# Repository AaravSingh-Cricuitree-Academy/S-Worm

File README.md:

# S-Worm
_Swarm based Watch operations for rescue missions_

## Basic architechtural overview-
Essentially its a system of 2 different types of drones
1) The recon
2) The rescuer
   
And also

-> Ground station

-> The ground station uses TDMA architechture to direct ALL the drones.

-> This is intended to be used in situations of disaster like earthquakes, tsunamis, bombings ,and/or mapping out complex terrain. 

Both share the same flight controller and ESC board. The difference in them is speciality boards which are unique to the respective drone, defined below-

-> The recon's speciality board is equiped with a Camera and LIDAR which hovers over terrain to map it out and then stores it. After a full map out it sends the data to the ground station where the data is processed and the area is divided into zones and high risk areas.

-> The rescue is equipped with a Mic, GPR to, Thermal and regular camera all processed by a PI hat 2 to look for human signals even under debris.

_Check [Hardware ReadMe](Hardware/Hardware_ReadMe.md) to have an in-depth
 overview of exactly what has been built ;)_

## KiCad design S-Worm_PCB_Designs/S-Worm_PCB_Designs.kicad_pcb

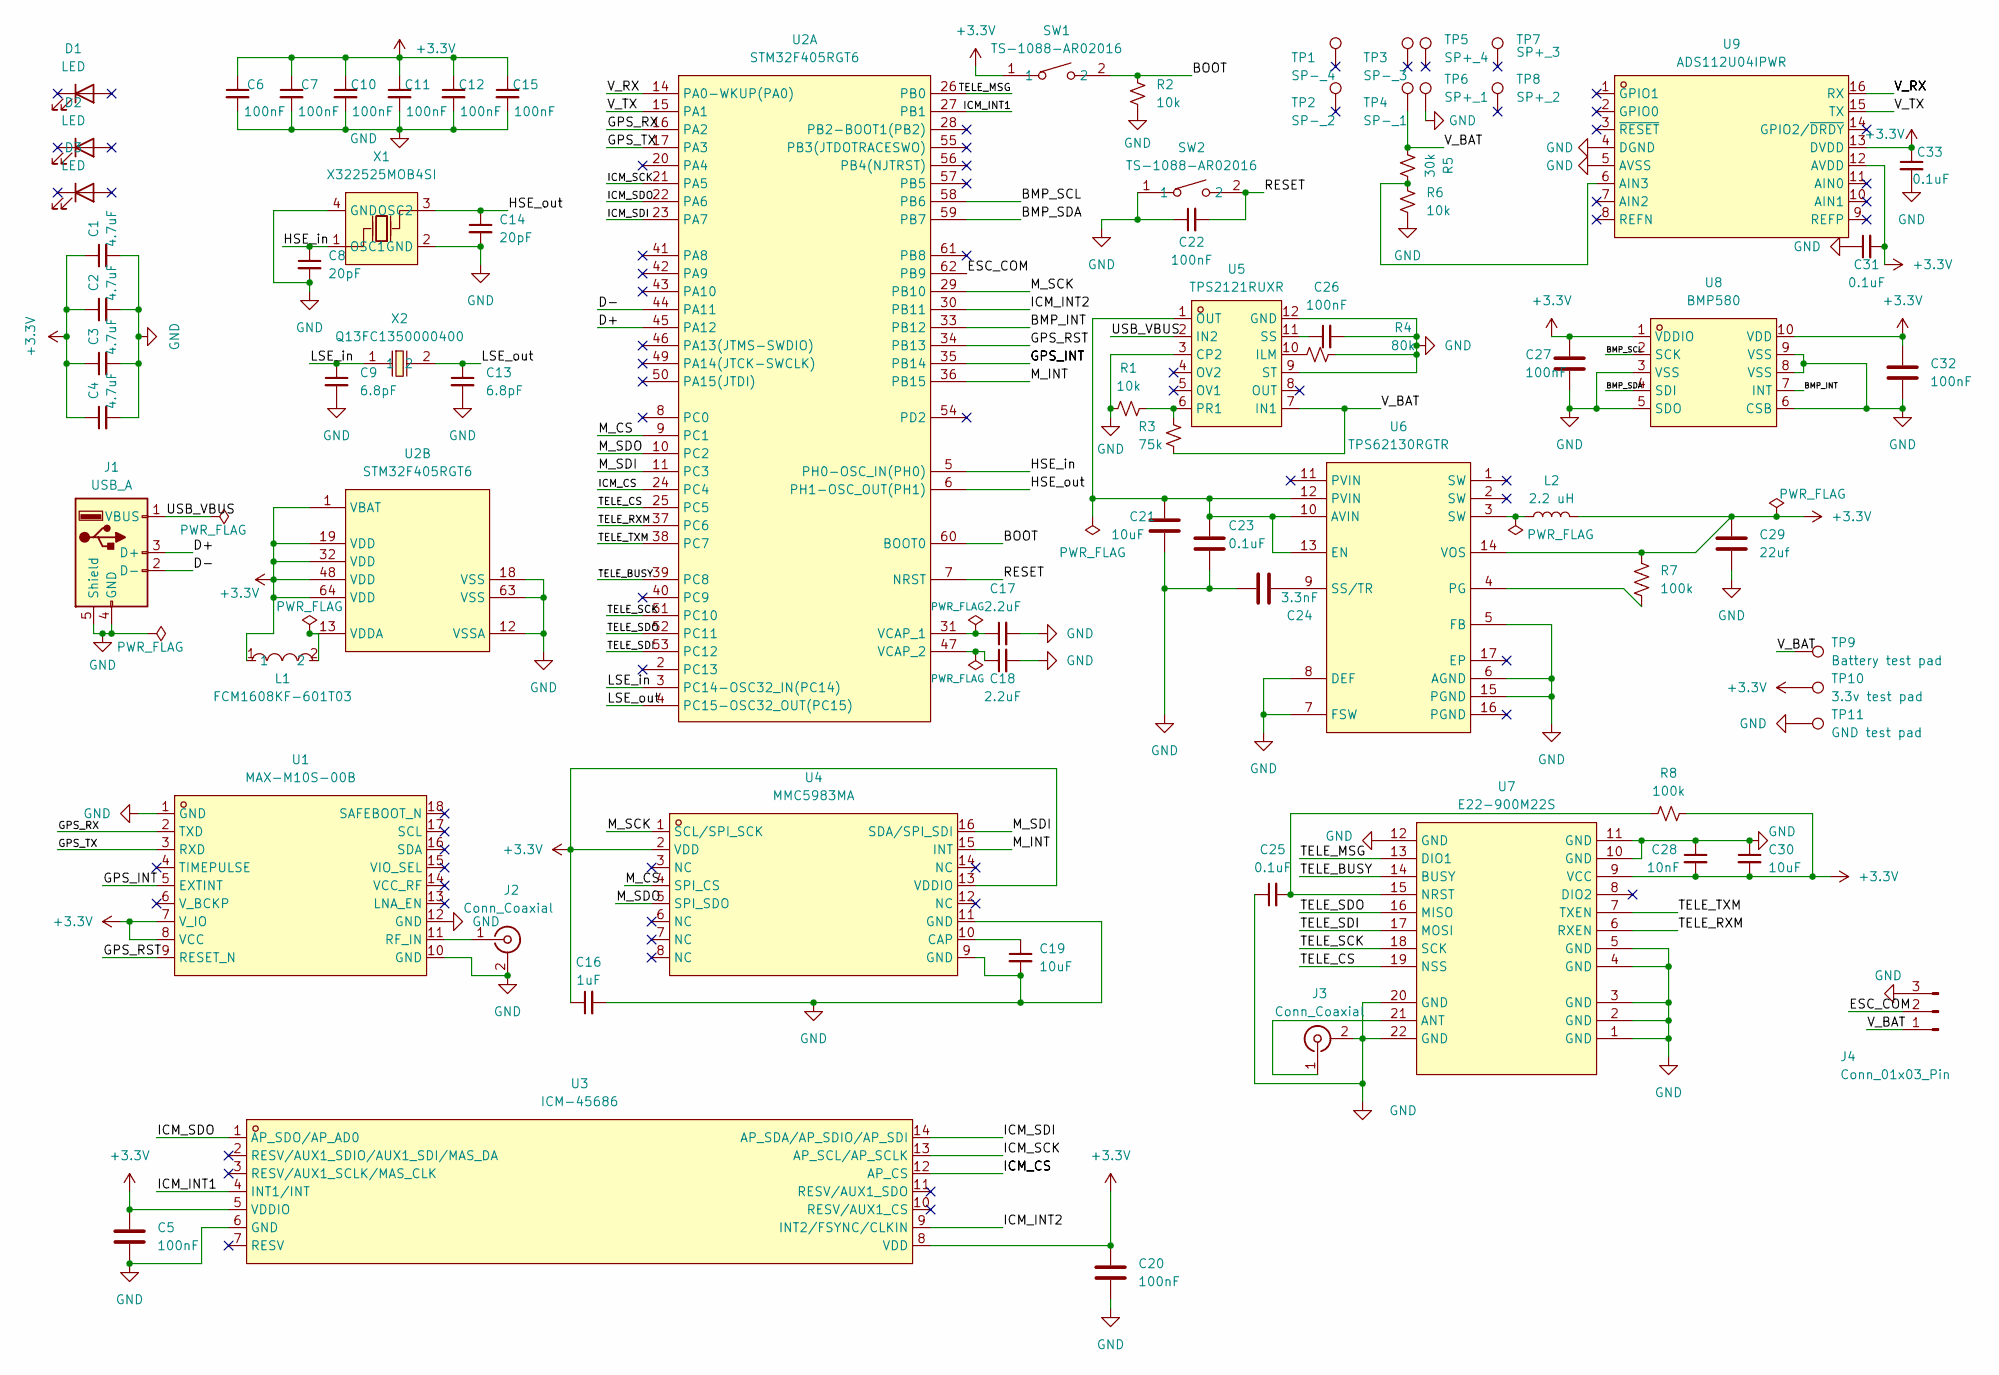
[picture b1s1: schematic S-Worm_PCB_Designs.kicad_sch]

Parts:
C1, C2, C3, C4: 4.7uF; C_0402_1005Metric
C5, C6, C7, C10, C11, C12, C15, C20, C22, C26, C27, C32: 100nF; C_0402_1005Metric
C8, C14: 20pF; C_0402_1005Metric
C9, C13: 6.8pF; C_0402_1005Metric
C16: 1uF; C_0402_1005Metric
C17, C18: 2.2uF; C_0402_1005Metric
C19: 10uF; C_0805_2012Metric
C21, C30: 10uF; C_0402_1005Metric
C23, C25, C31, C33: 0.1uF; C_0402_1005Metric
C24: 3.3nF; C_0402_1005Metric
C28: 10nF; C_0402_1005Metric
C29: 22uf; C_0402_1005Metric
D1, D2, D3: LED; LED_0805_2012Metric
J1: USB_A; USB_A_CNCTech_1001-011-01101_Horizontal
J2, J3: Conn_Coaxial; U.FL_Hirose_U.FL-R-SMT-1_Vertical
J4: Conn_01x03_Pin; JST_ACH_BM03B-ACHSS-GAN-ETF_1x03-1MP_P1.20mm_Vertical
L1: FCM1608KF-601T03; L0603; MPN FCM1608KF-601T03; LCSC Part C141723
L2: 2.2 uH; L_0201_0603Metric
R1, R2: 10k; R_0201_0603Metric
R3: 75k; R_0402_1005Metric
R4: 80k; R_0402_1005Metric
R5: 30k; R_0402_1005Metric
R6: 10k; R_0402_1005Metric
R7, R8: 100k; R_0402_1005Metric
SW1, SW2: TS-1088-AR02016; SW-SMD_L3.9-W3.0-P4.45; MPN TS-1088-AR02016; LCSC Part C720477
TP1: SP-_4; TestPoint_Pad_4.0x4.0mm
TP2: SP-_2; TestPoint_Pad_4.0x4.0mm
TP3: SP-_3; TestPoint_Pad_4.0x4.0mm
TP4: SP-_1; TestPoint_Pad_4.0x4.0mm
TP5: SP+_4; TestPoint_Pad_4.0x4.0mm
TP6: SP+_1; TestPoint_Pad_4.0x4.0mm
TP7: SP+_3; TestPoint_Pad_4.0x4.0mm
TP8: SP+_2; TestPoint_Pad_4.0x4.0mm
TP9: Battery test pad; TestPoint_Pad_4.0x4.0mm
TP10: 3.3v test pad; TestPoint_Pad_4.0x4.0mm
TP11: GND test pad; TestPoint_Pad_4.0x4.0mm
U1: MAX-M10S-00B; SMD-18_L10.1-W9.7-P1.10-TL_SKG09F; MPN MAX-M10S-00B; LCSC Part C4153167
U2: STM32F405RGT6; LQFP-64_L10.0-W10.0-P0.50-LS12.0-BL; MPN STM32F405RGT6; LCSC Part C15742
U3: ICM-45686; LGA-14_L3.0-W2.5-P0.50-TL; MPN ICM-45686; LCSC Part C22459454
U4: MMC5983MA; LGA-16_L3.0-W3.0-P0.50-BL_SQ; MPN MMC5983MA; LCSC Part C404329
U5: TPS2121RUXR; VQFN-HR-12_L2.5-W2.0-P0.50-BL; MPN TPS2121RUXR; LCSC Part C485916
U6: TPS62130RGTR; QFN-16_L3.0-W3.0-P0.50-TL-EP1.7; MPN TPS62130RGTR; LCSC Part C43590
U7: E22-900M22S; WIRELM-SMD_E22-900M22S; MPN E22-900M22S; LCSC Part C411293
U8: BMP580; LGA-10_L2.0-W2.0-P0.50-TL_BMP580; MPN BMP580; LCSC Part C22391138
U9: ADS112U04IPWR; TSSOP-16_L5.0-W4.4-P0.65-LS6.4-BL; MPN ADS112U04IPWR; LCSC Part C701616
X1: X322525MOB4SI; CRYSTAL-SMD_4P-L3.2-W2.5-BL; MPN X322525MOB4SI; LCSC Part C9006
X2: Q13FC1350000400; FC-135R_L3.2-W1.5; MPN Q13FC13500004; LCSC Part C32346

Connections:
+3.3V: C1.1, C2.1, C3.1, C4.1, C5.1, C6.1, C7.1, C10.1, C11.1, C12.1, C15.1, C16.1, C20.1, C27.1, C28.2, C29.1, C30.2, C31.2, C32.1, C33.1, L1.1, L2.2, R7.1, R8.2, SW1.1, TP10.1, U1.7 (V_IO), U1.8 (VCC), U2.1 (VBAT), U2.19 (VDD), U2.32 (VDD), U2.48 (VDD), U2.64 (VDD), U3.5 (VDDIO), U3.8 (VDD), U4.2 (VDD), U4.13 (VDDIO), U6.14 (VOS), U7.9 (VCC), U8.1 (VDDIO), U8.10 (VDD), U9.12 (AVDD), U9.13 (DVDD)
/BMP_INT: U2.33 (PB12), U8.7 (INT)
/BMP_SCL: U2.58 (PB6), U8.2 (SCK)
/BMP_SDA: U2.59 (PB7), U8.4 (SDI)
/BOOT: R2.1, SW1.2, U2.60 (BOOT0)
/D+: J1.3 (D+), U2.45 (PA12)
/D-: J1.2 (D-), U2.44 (PA11)
/ESC_COM: J4.2, U2.62 (PB9)
/GPS_INT: U1.5 (EXTINT), U2.35 (PB14)
/GPS_RST: U1.9 (RESET_N), U2.34 (PB13)
/GPS_RX: U1.2 (TXD), U2.16 (PA2)
/GPS_TX: U1.3 (RXD), U2.17 (PA3)
/HSE_in: C8.1, U2.5 (PH0-OSC_IN(PH0)), X1.1 (OSC1)
/HSE_out: C14.1, U2.6 (PH1-OSC_OUT(PH1)), X1.3 (OSC2)
/ICM_CS: U2.24 (PC4), U3.12 (AP_CS)
/ICM_INT1: U2.27 (PB1), U3.4 (INT1/INT)
/ICM_INT2: U2.30 (PB11), U3.9 (INT2/FSYNC/CLKIN)
/ICM_SCK: U2.21 (PA5), U3.13 (AP_SCL/AP_SCLK)
/ICM_SDI: U2.23 (PA7), U3.14 (AP_SDA/AP_SDIO/AP_SDI)
/ICM_SDO: U2.22 (PA6), U3.1 (AP_SDO/AP_AD0)
/LSE_in: C9.1, U2.3 (PC14-OSC32_IN(PC14)), X2.1
/LSE_out: C13.1, U2.4 (PC15-OSC32_OUT(PC15)), X2.2
/M_CS: U2.9 (PC1), U4.4 (SPI_CS)
/M_INT: U2.36 (PB15), U4.15 (INT)
/M_SCK: U2.29 (PB10), U4.1 (SCL/SPI_SCK)
/M_SDI: U2.11 (PC3), U4.16 (SDA/SPI_SDI)
/M_SDO: U2.10 (PC2), U4.5 (SPI_SDO)
/RESET: C22.2, SW2.2, U2.7 (NRST)
/TELE_BUSY: U2.39 (PC8), U7.14 (BUSY)
/TELE_CS: U2.25 (PC5), U7.19 (NSS)
/TELE_MSG: U2.26 (PB0), U7.13 (DIO1)
/TELE_RXM: U2.37 (PC6), U7.6 (RXEN)
/TELE_SCK: U2.51 (PC10), U7.18 (SCK)
/TELE_SDI: U2.53 (PC12), U7.17 (MOSI)
/TELE_SDO: U2.52 (PC11), U7.16 (MISO)
/TELE_TXM: U2.38 (PC7), U7.7 (TXEN)
/USB_VBUS: J1.1 (VBUS), U5.2 (IN2)
/V_BAT: J4.1, R3.2, R5.1, TP4.1, TP9.1, U5.7 (IN1)
/V_RX: U2.14 (PA0-WKUP(PA0)), U9.16 (RX)
/V_TX: U2.15 (PA1), U9.15 (TX)
GND: C1.2, C2.2, C3.2, C4.2, C5.2, C6.2, C7.2, C8.2, C9.2, C10.2, C11.2, C12.2, C13.2, C14.2, C15.2, C16.2, C17.2, C18.2, C19.2, C20.2, C21.2, C22.1, C23.2, C24.2, C25.1, C26.2, C27.2, C28.1, C29.2, C30.1, C31.1, C32.2, C33.2, J1.4 (GND), J1.5 (Shield), J2.2 (Ext), J3.2 (Ext), J4.3, J4.MP, R1.1, R2.2, R4.2, R6.2, SW2.1, TP6.1, TP11.1, U1.1 (GND), U1.10 (GND), U1.12 (GND), U2.12 (VSSA), U2.18 (VSS), U2.63 (VSS), U3.6 (GND), U4.9 (GND), U4.11 (GND), U5.3 (CP2), U5.9 (ST), U5.12 (GND), U6.5 (FB), U6.6 (AGND), U6.7 (FSW), U6.8 (DEF), U6.15 (PGND), U7.1 (GND), U7.2 (GND), U7.3 (GND), U7.4 (GND), U7.5 (GND), U7.10 (GND), U7.11 (GND), U7.12 (GND), U7.20 (GND), U7.22 (GND), U8.3 (VSS), U8.5 (SDO), U8.6 (CSB), U8.8 (VSS), U8.9 (VSS), U9.4 (DGND), U9.5 (AVSS), X1.2 (GND), X1.4 (GND)
unnamed: J2.1 (In), U1.11 (RF_IN)
unnamed: J3.1 (In), U7.21 (ANT)
unnamed: L2.1, U6.3 (SW)
unnamed: C17.1, U2.31 (VCAP_1)
unnamed: C18.1, U2.47 (VCAP_2)
unnamed: L1.2, U2.13 (VDDA)
unnamed: C19.1, U4.10 (CAP)
unnamed: R4.1, U5.10 (ILM)
unnamed: R1.2, R3.1, U5.6 (PR1)
unnamed: C26.1, U5.11 (SS)
unnamed: C21.1, C23.1, U5.1 (OUT), U6.10 (AVIN), U6.12 (PVIN), U6.13 (EN)
unnamed: R7.2, U6.4 (PG)
unnamed: C24.1, U6.9 (SS/TR)
unnamed: C25.2, R8.1, U7.15 (NRST)
unnamed: R5.2, R6.1, U9.6 (AIN3)

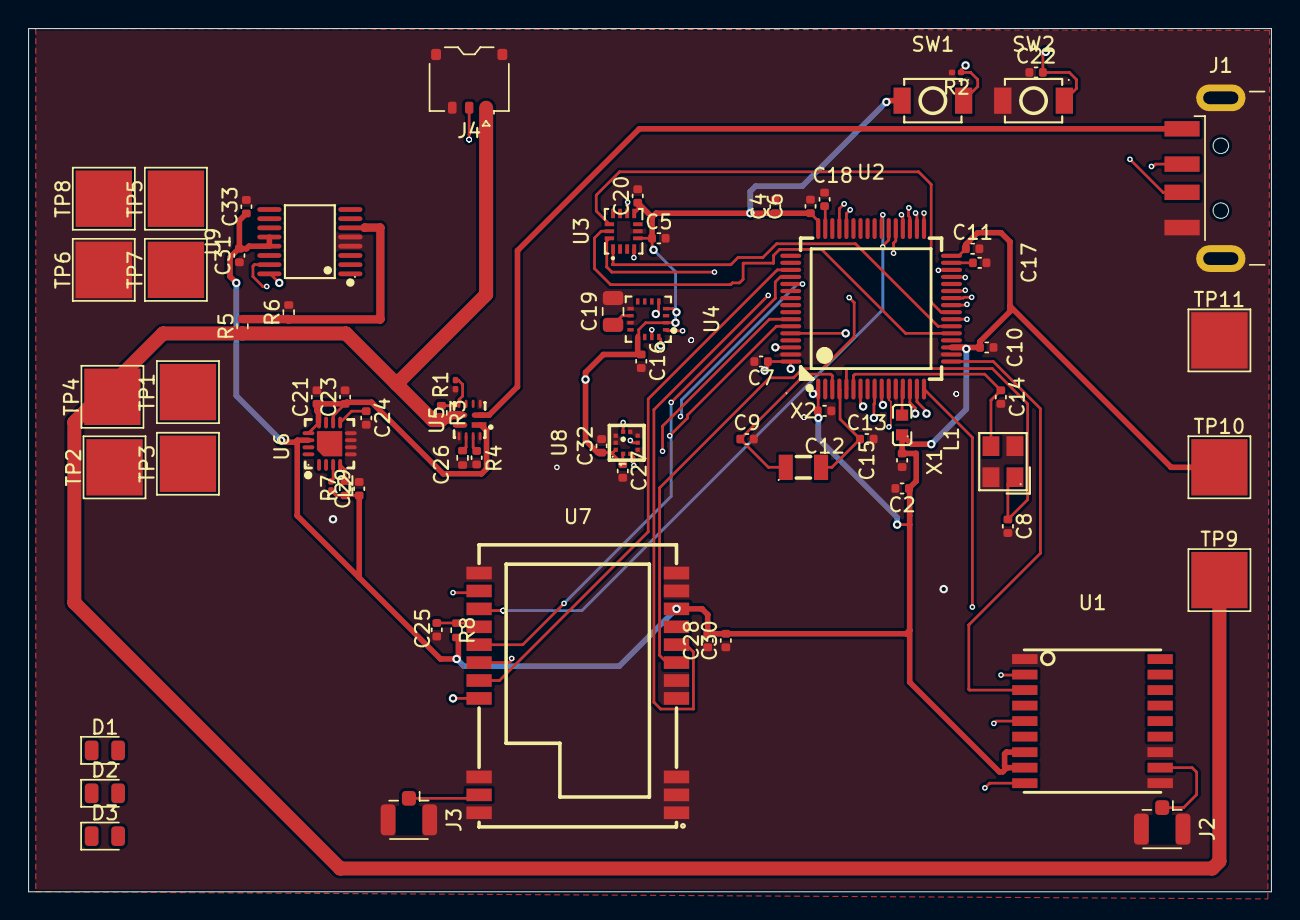
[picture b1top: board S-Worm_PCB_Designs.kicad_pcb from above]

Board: 4 copper layers, 88.1 x 61.2 mm, 72 parts (0 on the bottom side), 56 nets.

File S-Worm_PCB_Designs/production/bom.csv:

Designator,Footprint,Quantity,Value,LCSC Part #
"C10, C11, C12, C15, C20, C22, C26, C27, C32, C5, C6, C7",0402,12,100nF,
"C13, C9",0402,2,6.8pF,
"C14, C8",0402,2,20pF,
C16,0402,1,1uF,
"C17, C18",0402,2,2.2uF,
C19,0805,1,10uF,
"C2, C4",0402,2,4.7uF,
"C21, C30",0402,2,10uF,
"C23, C25, C31, C33",0402,4,0.1uF,
C24,0402,1,3.3nF,
C28,0402,1,10nF,
C29,0402,1,22uf,
"D1, D2, D3",0805,3,LED,
J1,USB_A_CNCTech_1001-011-01101_Horizontal,1,USB_A,
"J2, J3",U.FL_Hirose_U.FL-R-SMT-1_Vertical,2,Conn_Coaxial,
J4,JST_ACH_BM03B-ACHSS-GAN-ETF_1x03-1MP_P1.20mm_Vertical,1,Conn_01x03_Pin,
L1,L0603,1,FCM1608KF-601T03,C141723
L2,0201,1,2.2 uH,
"R1, R2",0201,2,10k,
R3,0402,1,75k,
R4,0402,1,80k,
R5,0402,1,30k,
R6,0402,1,10k,
"R7, R8",0402,2,100k,
"SW1, SW2",SW-SMD_L3.9-W3.0-P4.45,2,TS-1088-AR02016,C720477
TP1,TestPoint_Pad_4.0x4.0mm,1,SP-_4,
TP10,TestPoint_Pad_4.0x4.0mm,1,3.3v test pad,
TP11,TestPoint_Pad_4.0x4.0mm,1,GND test pad,
TP2,TestPoint_Pad_4.0x4.0mm,1,SP-_2,
TP3,TestPoint_Pad_4.0x4.0mm,1,SP-_3,
TP4,TestPoint_Pad_4.0x4.0mm,1,SP-_1,
TP5,TestPoint_Pad_4.0x4.0mm,1,SP+_4,
TP6,TestPoint_Pad_4.0x4.0mm,1,SP+_1,
TP7,TestPoint_Pad_4.0x4.0mm,1,SP+_3,
TP8,TestPoint_Pad_4.0x4.0mm,1,SP+_2,
TP9,TestPoint_Pad_4.0x4.0mm,1,Battery test pad,
U1,SMD-18_L10.1-W9.7-P1.10-TL_SKG09F,1,MAX-M10S-00B,C4153167
U2,LQFP-64_L10.0-W10.0-P0.50-LS12.0-BL,1,STM32F405RGT6,C15742
U3,LGA-14_L3.0-W2.5-P0.50-TL,1,ICM-45686,C22459454
U4,LGA-16_L3.0-W3.0-P0.50-BL_SQ,1,MMC5983MA,C404329
U5,VQFN-HR-12_L2.5-W2.0-P0.50-BL,1,TPS2121RUXR,C485916
U6,QFN-16_L3.0-W3.0-P0.50-TL-EP1.7,1,TPS62130RGTR,C43590
U7,WIRELM-SMD_E22-900M22S,1,E22-900M22S,C411293
U8,LGA-10_L2.0-W2.0-P0.50-TL_BMP580,1,BMP580,C22391138
U9,TSSOP-16_L5.0-W4.4-P0.65-LS6.4-BL,1,ADS112U04IPWR,C701616
X1,CRYSTAL-SMD_4P-L3.2-W2.5-BL,1,X322525MOB4SI,C9006
X2,FC-135R_L3.2-W1.5,1,Q13FC1350000400,C32346

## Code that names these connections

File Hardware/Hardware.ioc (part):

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Mcu.Name=STM32F405RGTx
Mcu.Package=LQFP64
Mcu.UserName=STM32F405RGTx
PA0-WKUP.GPIOParameters=GPIO_Label
PA0-WKUP.GPIO_Label=V_TX
PA0-WKUP.Mode=Asynchronous
PA0-WKUP.Signal=UART4_TX
PA1.GPIOParameters=GPIO_Label
PA1.GPIO_Label=V_RX
PA1.Mode=Asynchronous
PA1.Signal=UART4_RX
PA11.Mode=Device_Only
PA11.Signal=USB_OTG_FS_DM
PA12.Mode=Device_Only
PA12.Signal=USB_OTG_FS_DP
PA2.GPIOParameters=GPIO_Label
PA2.GPIO_Label=GPS_TX
PA2.Mode=Asynchronous
PA2.Signal=USART2_TX
PA3.GPIOParameters=GPIO_Label
PA3.GPIO_Label=GPS_RX
PA3.Mode=Asynchronous
PA3.Signal=USART2_RX
PA5.GPIOParameters=GPIO_Label
PA5.GPIO_Label=IMU_SCK
PA5.Mode=Full_Duplex_Master
PA5.Signal=SPI1_SCK
PA6.GPIOParameters=GPIO_Label
PA6.GPIO_Label=IMU_SDO
PA6.Mode=Full_Duplex_Master
PA6.Signal=SPI1_MISO
PA7.GPIOParameters=GPIO_Label
PA7.GPIO_Label=IMU_SDI
PA7.Mode=Full_Duplex_Master
PA7.Signal=SPI1_MOSI
PA9.GPIOParameters=GPIO_Label
PA9.GPIO_Label=ESC_COM
PA9.Mode=Half_duplex(single_wire_mode)
PA9.Signal=USART1_TX
PB0.GPIOParameters=GPIO_Label
PB0.GPIO_Label=TELE_MSG
PB0.Signal=GPIO_Output
PB1.GPIOParameters=GPIO_Label
PB1.GPIO_Label=IMU_INT1
PB1.Signal=GPXTI1
PB10.GPIOParameters=GPIO_Label
PB10.GPIO_Label=M_SCK
PB10.Mode=Full_Duplex_Master
PB10.Signal=SPI2_SCK
PB11.GPIOParameters=GPIO_Label
PB11.GPIO_Label=IMU_INT2
PB11.Signal=GPXTI11
PB12.GPIOParameters=GPIO_Label
PB12.GPIO_Label=BMP_INT
PB12.Signal=GPXTI12
PB13.GPIOParameters=GPIO_Label
PB13.GPIO_Label=GPS_RST
PB13.Signal=GPIO_Output
PB14.GPIOParameters=GPIO_Label
PB14.GPIO_Label=GPS_INT
PB14.Signal=GPXTI14
PB15.GPIOParameters=GPIO_Label
PB15.GPIO_Label=M_INT
PB15.Signal=GPXTI15
PB5.Mode=SMBus-Alert-mode
PB5.Signal=I2C1_SMBA
PB6.GPIOParameters=GPIO_Label
PB6.GPIO_Label=BMP_SCL
PB6.Mode=SMBus-Alert-mode
PB6.Signal=I2C1_SCL
PB7.GPIOParameters=GPIO_Label
PB7.GPIO_Label=BMP_SDA
PB7.Mode=SMBus-Alert-mode
PB7.Signal=I2C1_SDA
PC1.GPIOParameters=GPIO_Label
PC1.GPIO_Label=M_CS
PC1.Signal=GPIO_Output
PC10.GPIOParameters=GPIO_Label
PC10.GPIO_Label=TELE_SCK
PC10.Mode=Full_Duplex_Master
PC10.Signal=SPI3_SCK
PC11.GPIOParameters=GPIO_Label
PC11.GPIO_Label=TELE_SDO
PC11.Mode=Full_Duplex_Master
PC11.Signal=SPI3_MISO
PC12.GPIOParameters=GPIO_Label
PC12.GPIO_Label=TELE_SDI
PC12.Mode=Full_Duplex_Master
PC12.Signal=SPI3_MOSI
PC14-OSC32_IN.GPIOParameters=GPIO_Label
PC14-OSC32_IN.GPIO_Label=LSE_IN
PC14-OSC32_IN.Mode=LSE-External-Oscillator
PC14-OSC32_IN.Signal=RCC_OSC32_IN
PC15-OSC32_OUT.GPIOParameters=GPIO_Label
PC15-OSC32_OUT.GPIO_Label=LSE_OUT
PC15-OSC32_OUT.Mode=LSE-External-Oscillator
PC15-OSC32_OUT.Signal=RCC_OSC32_OUT
PC2.GPIOParameters=GPIO_Label
PC2.GPIO_Label=M_SDO
PC2.Mode=Full_Duplex_Master
PC2.Signal=SPI2_MISO
PC3.GPIOParameters=GPIO_Label
PC3.GPIO_Label=M_SDI
PC3.Mode=Full_Duplex_Master
PC3.Signal=SPI2_MOSI
PC4.GPIOParameters=GPIO_Label
PC4.GPIO_Label=IMU_CS
PC4.Signal=GPIO_Output
PC5.GPIOParameters=GPIO_Label
PC5.GPIO_Label=TELE_CS
PC5.Signal=GPIO_Output
PC6.GPIOParameters=GPIO_Label
PC6.GPIO_Label=TELE_RXM
PC6.Signal=GPIO_Output
PC7.GPIOParameters=GPIO_Label
PC7.GPIO_Label=TELE_TXM
PC7.Signal=GPIO_Output
PC8.GPIOParameters=GPIO_Label
PC8.GPIO_Label=TELE_BUSY
PC8.Signal=GPIO_Input
PH0-OSC_IN.GPIOParameters=GPIO_Label
PH0-OSC_IN.GPIO_Label=HSE_IN
PH0-OSC_IN.Mode=HSE-External-Oscillator
PH0-OSC_IN.Signal=RCC_OSC_IN
PH1-OSC_OUT.GPIOParameters=GPIO_Label
PH1-OSC_OUT.GPIO_Label=HSE_OUT
PH1-OSC_OUT.Mode=HSE-External-Oscillator
PH1-OSC_OUT.Signal=RCC_OSC_OUT
RCC.HSE_VALUE=25000000
RCC.SYSCLKFreq_VALUE=16000000
board=custom

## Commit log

2026-06-07 Create Hardware_README
2026-06-07 Create Hardware_ReadMe
    Placeholder
2026-06-07 Update Hardware_ReadMe
2026-06-07 Create Software_ReadMe
2026-06-07 Uhm test?
2026-06-07 Pre error i guess
2026-06-07 worked thank god
2026-06-07 done for today i hope
2026-06-08 bruh
2026-06-09 req?
2026-06-10 switching the module lol
2026-06-10 switched
2026-06-10 bruh2
2026-06-10 power_aaa
2026-06-12 it didnt commite yesterday i dunno why
2026-06-12 adc wow
2026-06-12 adc aaa
2026-06-13 WHAT
2026-06-15 i dunno
2026-06-19 almost there
